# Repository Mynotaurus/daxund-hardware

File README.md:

# Daxund Hardware

kicad files for [daxund](https://zatzhing.me/blog/daxund)

terms of use is you can do what you want with it as long as you dont use AI. use your brains use your hands

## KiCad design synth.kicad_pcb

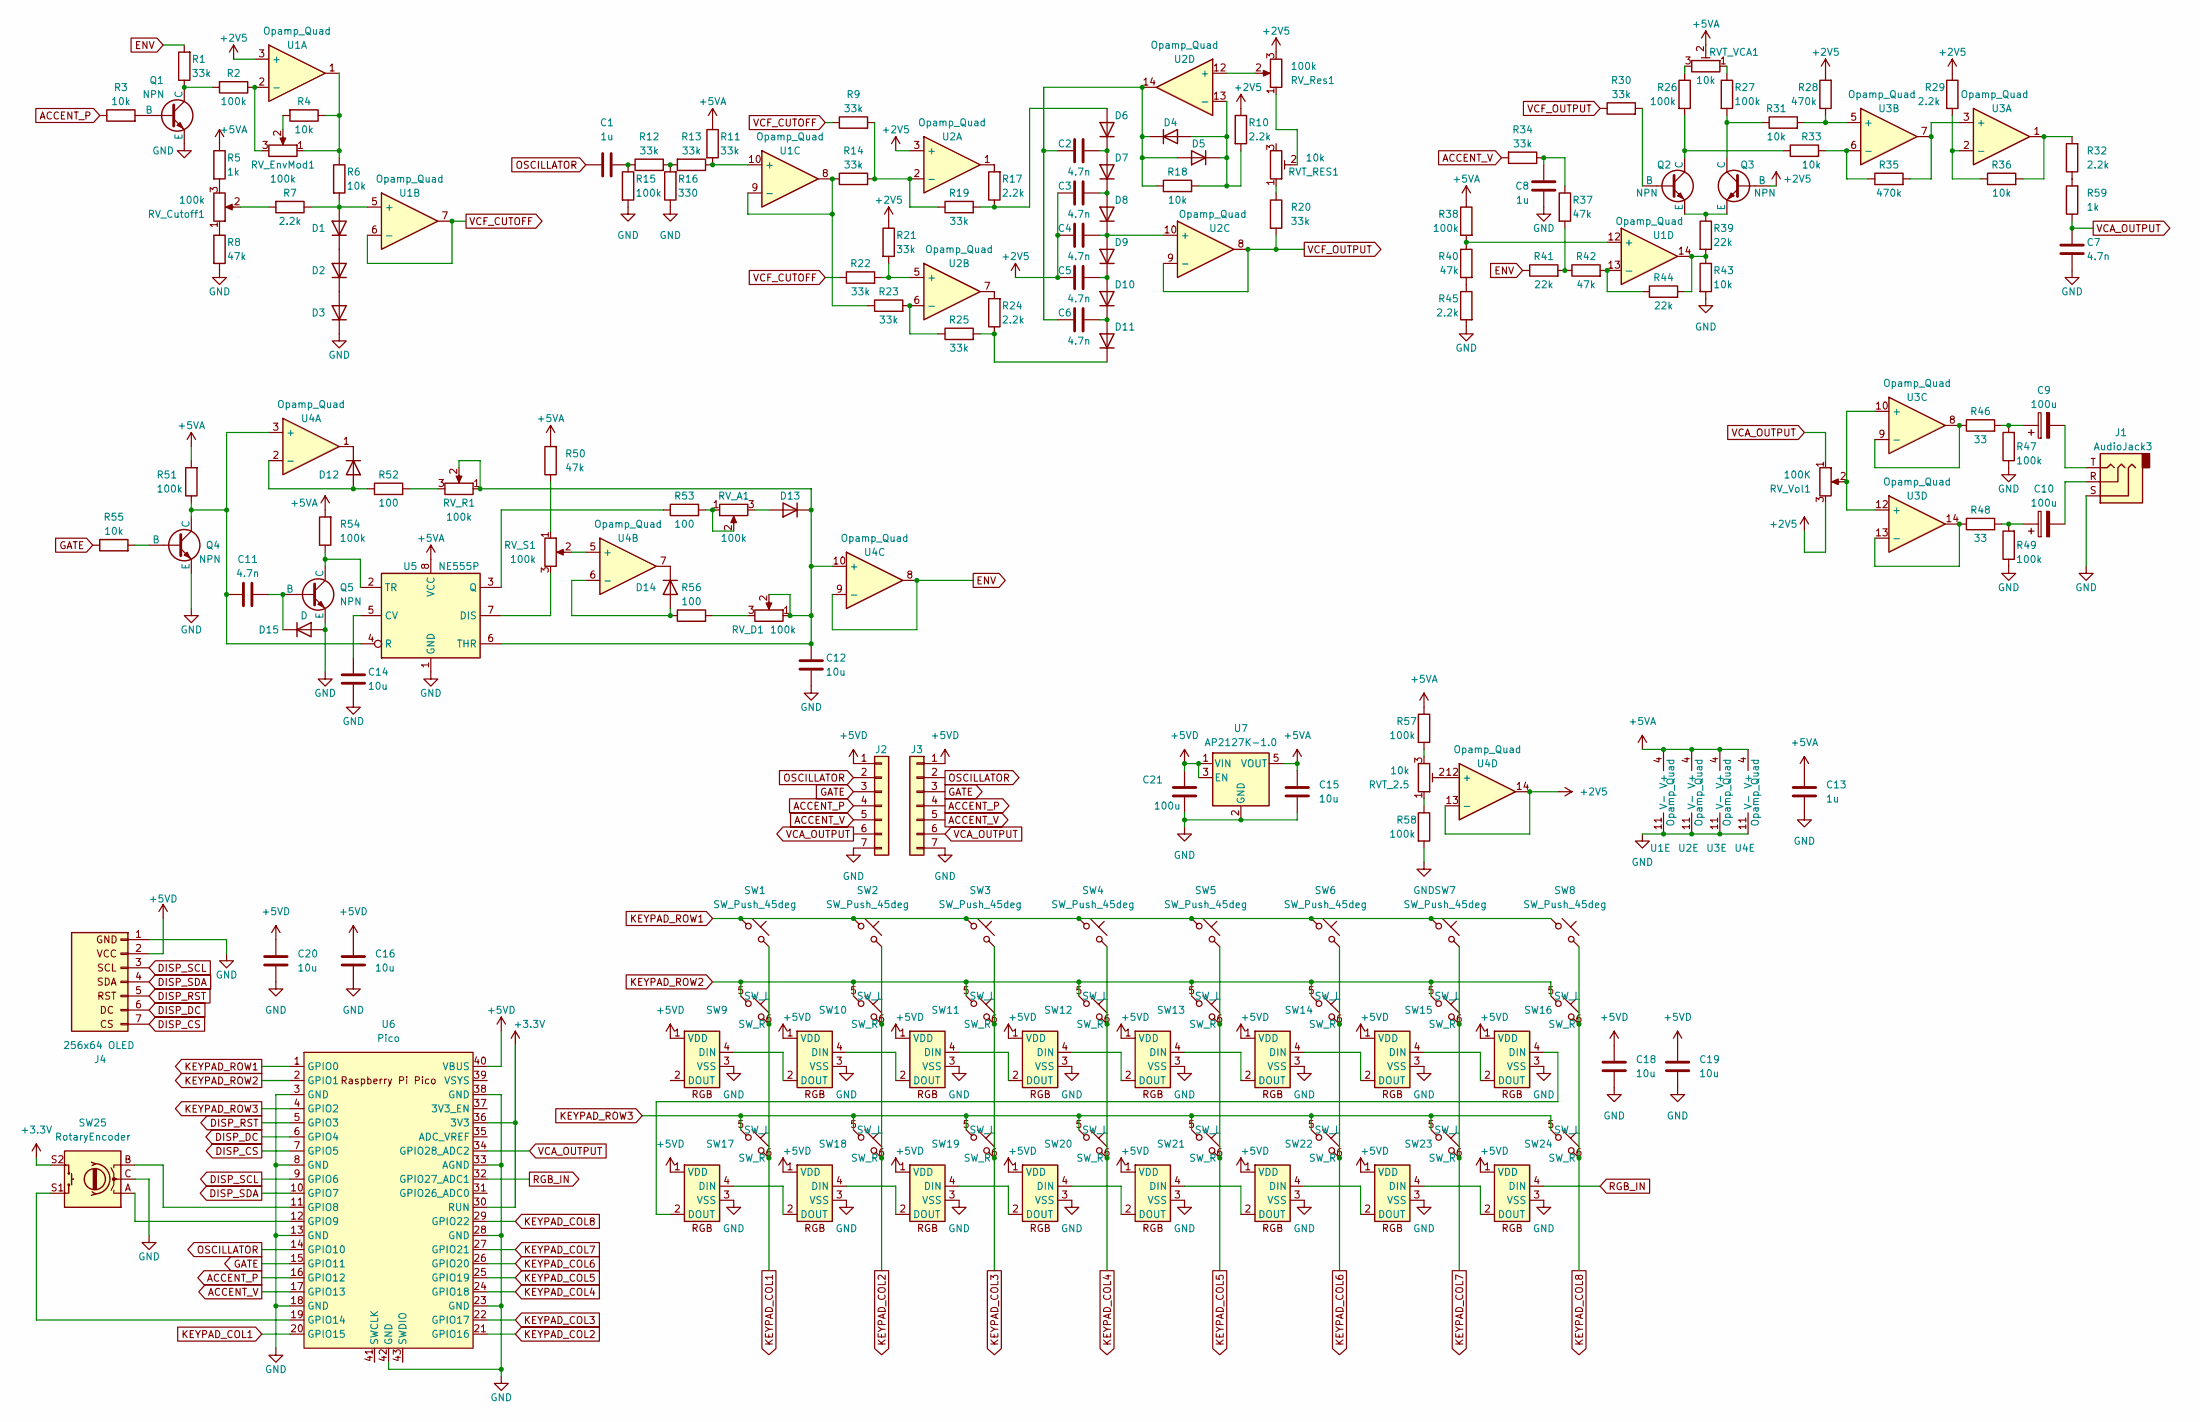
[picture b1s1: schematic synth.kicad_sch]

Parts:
C1, C8, C13: 1u; C_Rect_L7.0mm_W2.5mm_P5.00mm
C2, C3, C4, C5, C6, C7, C11: 4.7n; C_Rect_L7.0mm_W2.5mm_P5.00mm
C9, C10, C21: 100u; CP_Radial_D5.0mm_P2.50mm
C12, C14, C15, C16, C18, C19, C20: 10u; C_Rect_L7.0mm_W2.5mm_P5.00mm
D1, D2, D3, D4, D5, D6, D7, D8, D9, D10, D11, D12, D13, D14, D15: D; D_DO-35_SOD27_P7.62mm_Horizontal
J1: AudioJack3; Jack_3.5mm_CUI_SJ1-3525N_Horizontal
J2, J3: Conn_01x07; PinHeader_1x07_P2.54mm_Horizontal
J4: 256x64 OLED; oled
Q1, Q2, Q3, Q4, Q5: NPN; TO-92_Inline
R1, R9, R11, R12, R13, R14, R19, R20, R21, R22, R23, R25, R30, R34: 33k; R_Axial_DIN0207_L6.3mm_D2.5mm_P10.16mm_Horizontal
R2, R15, R26, R27, R38, R47, R49, R51, R54, R57, R58: 100k; R_Axial_DIN0207_L6.3mm_D2.5mm_P10.16mm_Horizontal
R3, R4, R6, R18, R31, R33, R36, R43, R55: 10k; R_Axial_DIN0207_L6.3mm_D2.5mm_P10.16mm_Horizontal
R5, R59: 1k; R_Axial_DIN0207_L6.3mm_D2.5mm_P10.16mm_Horizontal
R7, R10, R17, R24, R29, R32, R45: 2.2k; R_Axial_DIN0207_L6.3mm_D2.5mm_P10.16mm_Horizontal
R8, R37, R40, R42, R50: 47k; R_Axial_DIN0207_L6.3mm_D2.5mm_P10.16mm_Horizontal
R16: 330; R_Axial_DIN0207_L6.3mm_D2.5mm_P10.16mm_Horizontal
R28, R35: 470k; R_Axial_DIN0207_L6.3mm_D2.5mm_P10.16mm_Horizontal
R39, R41, R44: 22k; R_Axial_DIN0207_L6.3mm_D2.5mm_P10.16mm_Horizontal
R46, R48: 33; R_Axial_DIN0207_L6.3mm_D2.5mm_P10.16mm_Horizontal
R52, R53, R56: 100; R_Axial_DIN0207_L6.3mm_D2.5mm_P10.16mm_Horizontal
RVT_2.5: 10k; Potentiometer_ACP_CA9-V10_Vertical_Hole
RVT_RES1: 10k; Potentiometer_ACP_CA9-V10_Vertical_Hole
RVT_VCA1: 10k; Potentiometer_ACP_CA9-V10_Vertical_Hole
RV_A1: 100k; Potentiometer_Bourns_PTV09A-1_Single_Vertical
RV_Cutoff1: 100k; Potentiometer_Bourns_PTV09A-1_Single_Vertical
RV_D1: 100k; Potentiometer_Bourns_PTV09A-1_Single_Vertical
RV_EnvMod1: 100k; Potentiometer_Bourns_PTV09A-1_Single_Vertical
RV_R1: 100k; Potentiometer_Bourns_PTV09A-1_Single_Vertical
RV_Res1: 100k; Potentiometer_Bourns_PTV09A-1_Single_Vertical
RV_S1: 100k; Potentiometer_Bourns_PTV09A-1_Single_Vertical
RV_Vol1: 100K; Potentiometer_Bourns_PTV09A-1_Single_Vertical
SW1, SW2, SW3, SW4, SW5, SW6, SW7, SW8: SW_Push_45deg; SW_Cherry_MX_1.00u_PCB
SW9, SW10, SW11, SW12, SW13, SW14, SW15, SW16, SW17, SW18, SW19, SW20, SW21, SW22, SW23, SW24: button
SW25: RotaryEncoder; RotaryEncoder_Alps_EC11E-Switch_Vertical_H20mm
U1, U2, U3, U4: Opamp_Quad; DIP-14_W7.62mm
U5: NE555P; DIP-8_W7.62mm
U6: Pico; RPi_Pico_SMD_TH
U7: AP2127K-1.0; SOT-23-5

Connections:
+2V5: C3.1, C4.1, C5.1, Q3.2 (B), R10.1, R21.1, R28.2, R29.1, RV_Res1.3, RV_Vol1.3, U1.3 (+), U2.3 (+), U4.13 (-), U4.14
+3.3V: SW25.S2, U6.30 (RUN), U6.36 (3V3)
+5VA: C13.1, C15.1, R5.1, R11.1, R38.1, R50.2, R51.2, R54.2, R57.1, RVT_VCA1.2, U1.4 (V+), U2.4 (V+), U3.4 (V+), U4.4 (V+), U5.8 (VCC), U7.5 (VOUT)
+5VD: C16.1, C18.1, C19.1, C20.1, C21.1, J2.1, J3.1, J4.2 (VCC), SW9.1 (VDD), SW10.1 (VDD), SW11.1 (VDD), SW12.1 (VDD), SW13.1 (VDD), SW14.1 (VDD), SW15.1 (VDD), SW16.1 (VDD), SW17.1 (VDD), SW18.1 (VDD), SW19.1 (VDD), SW20.1 (VDD), SW21.1 (VDD), SW22.1 (VDD), SW23.1 (VDD), SW24.1 (VDD), U6.40 (VBUS), U7.1 (VIN), U7.3 (EN)
ACCENT_P: J2.4, J3.4, R3.1, U6.16 (GPIO12)
ACCENT_V: J2.5, J3.5, R34.2, U6.17 (GPIO13)
DISP_CS: J4.7 (CS), U6.7 (GPIO5)
DISP_DC: J4.6 (DC), U6.6 (GPIO4)
DISP_RST: J4.5 (RST), U6.5 (GPIO3)
DISP_SCL: J4.3 (SCL), U6.9 (GPIO6)
DISP_SDA: J4.4 (SDA), U6.10 (GPIO7)
ENV: R1.2, R41.1, U4.8, U4.9 (-)
GATE: J2.3, J3.3, R55.1, U6.15 (GPIO11)
GND: C7.2, C8.2, C12.2, C13.2, C14.1, C15.2, C16.2, C18.2, C19.2, C20.2, C21.2, D3.1 (K), D15.2 (A), J1.S, J2.7, J3.7, J4.1 (GND), Q1.3 (E), Q4.3 (E), Q5.3 (E), R8.2, R15.2, R16.1, R43.2, R45.2, R47.1, R49.1, R58.2, SW9.3 (VSS), SW10.3 (VSS), SW11.3 (VSS), SW12.3 (VSS), SW13.3 (VSS), SW14.3 (VSS), SW15.3 (VSS), SW16.3 (VSS), SW17.3 (VSS), SW18.3 (VSS), SW19.3 (VSS), SW20.3 (VSS), SW21.3 (VSS), SW22.3 (VSS), SW23.3 (VSS), SW24.3 (VSS), SW25.C, U1.11 (V-), U2.11 (V-), U3.11 (V-), U4.11 (V-), U5.1 (GND), U6.3 (GND), U6.8 (GND), U6.13 (GND), U6.18 (GND), U6.23 (GND), U6.28 (GND), U6.33 (AGND), U6.38 (GND), U6.42 (GND), U7.2 (GND)
KEYPAD_COL1: SW1.2, SW9.6 (SW_R), SW17.6 (SW_R), U6.20 (GPIO15)
KEYPAD_COL2: SW2.2, SW10.6 (SW_R), SW18.6 (SW_R), U6.21 (GPIO16)
KEYPAD_COL3: SW3.2, SW11.6 (SW_R), SW19.6 (SW_R), U6.22 (GPIO17)
KEYPAD_COL4: SW4.2, SW12.6 (SW_R), SW20.6 (SW_R), U6.24 (GPIO18)
KEYPAD_COL5: SW5.2, SW13.6 (SW_R), SW21.6 (SW_R), U6.25 (GPIO19)
KEYPAD_COL6: SW6.2, SW14.6 (SW_R), SW22.6 (SW_R), U6.26 (GPIO20)
KEYPAD_COL7: SW7.2, SW15.6 (SW_R), SW23.6 (SW_R), U6.27 (GPIO21)
KEYPAD_COL8: SW8.2, SW16.6 (SW_R), SW24.6 (SW_R), U6.29 (GPIO22)
KEYPAD_ROW1: SW1.1, SW2.1, SW3.1, SW4.1, SW5.1, SW6.1, SW7.1, SW8.1, U6.1 (GPIO0)
KEYPAD_ROW2: SW9.5 (SW_L), SW10.5 (SW_L), SW11.5 (SW_L), SW12.5 (SW_L), SW13.5 (SW_L), SW14.5 (SW_L), SW15.5 (SW_L), SW16.5 (SW_L), U6.2 (GPIO1)
KEYPAD_ROW3: SW17.5 (SW_L), SW18.5 (SW_L), SW19.5 (SW_L), SW20.5 (SW_L), SW21.5 (SW_L), SW22.5 (SW_L), SW23.5 (SW_L), SW24.5 (SW_L), U6.4 (GPIO2)
unnamed: C1.1, R12.1, R15.1
unnamed: C8.1, R34.1, R37.1
unnamed: C9.1, R46.2, R47.2
unnamed: C9.2, J1.T
unnamed: C10.1, R48.2, R49.2
unnamed: C10.2, J1.R
unnamed: D1.2 (A), R6.2, R7.1, U1.5 (+)
unnamed: D1.1 (K), D2.2 (A)
unnamed: D2.1 (K), D3.2 (A)
unnamed: D4.2 (A), D5.1 (K), R10.2, R18.2, U2.13 (-)
unnamed: C2.1, C6.1, D4.1 (K), D5.2 (A), R18.1, U2.14
unnamed: D6.2 (A), R17.1, R19.2
unnamed: C2.2, D6.1 (K), D7.2 (A)
unnamed: C3.2, D7.1 (K), D8.2 (A)
unnamed: C4.2, D8.1 (K), D9.2 (A), U2.10 (+)
unnamed: C5.2, D9.1 (K), D10.2 (A)
unnamed: C6.2, D10.1 (K), D11.2 (A)
unnamed: D11.1 (K), R24.1, R25.2
unnamed: D12.2 (A), R52.1, U4.2 (-)
unnamed: D12.1 (K), U4.1
unnamed: D13.2 (A), RV_A1.3
unnamed: C12.1, D13.1 (K), RV_D1.1, RV_D1.2, RV_R1.1, RV_R1.2, U4.10 (+), U5.6 (THR)
unnamed: D14.2 (A), R56.1, U4.6 (-)
unnamed: D14.1 (K), U4.7
unnamed: C11.2, D15.1 (K), Q5.2 (B)
unnamed: Q1.2 (B), R3.2
unnamed: Q1.1 (C), R1.1, R2.2
unnamed: Q2.2 (B), R30.2
unnamed: Q2.1 (C), R26.2, R33.1
unnamed: Q2.3 (E), Q3.3 (E), R39.1
unnamed: Q3.1 (C), R27.2, R31.1
unnamed: Q4.2 (B), R55.2
unnamed: C11.1, Q4.1 (C), R51.1, U4.3 (+), U5.4 (R)
unnamed: Q5.1 (C), R54.1, U5.2 (TR)
unnamed: R4.1, R6.1, RV_EnvMod1.1, U1.1
unnamed: R4.2, RV_EnvMod1.2
unnamed: R5.2, RV_Cutoff1.3
unnamed: R7.2, RV_Cutoff1.2
unnamed: R8.1, RV_Cutoff1.1
unnamed: R12.2, R13.2, R16.2
unnamed: R17.2, U2.1
unnamed: R20.1, RVT_RES1.1
unnamed: R24.2, U2.7
unnamed: R26.1, RVT_VCA1.3
unnamed: R27.1, RVT_VCA1.1
unnamed: R32.1, R59.2
unnamed: R32.2, R36.2, U3.1
unnamed: R37.2, R41.2, R42.1
unnamed: R39.2, R43.1, R44.2, U1.14
unnamed: R40.2, R45.1
unnamed: R50.1, RV_S1.1
unnamed: R52.2, RV_R1.3
unnamed: R53.2, RV_A1.1, RV_A1.2
unnamed: R56.2, RV_D1.3
unnamed: R57.2, RVT_2.5.3
unnamed: R58.1, RVT_2.5.1
unnamed: RVT_RES1.2, RV_Res1.1
unnamed: SW10.4 (DIN), SW11.2 (DOUT)
unnamed: SW9.4 (DIN), SW10.2 (DOUT)
unnamed: SW11.4 (DIN), SW12.2 (DOUT)
unnamed: SW12.4 (DIN), SW13.2 (DOUT)
unnamed: SW13.4 (DIN), SW14.2 (DOUT)
unnamed: SW14.4 (DIN), SW15.2 (DOUT)
unnamed: SW15.4 (DIN), SW16.2 (DOUT)
unnamed: SW16.4 (DIN), SW17.2 (DOUT)
unnamed: SW17.4 (DIN), SW18.2 (DOUT)
unnamed: SW18.4 (DIN), SW19.2 (DOUT)
unnamed: SW19.4 (DIN), SW20.2 (DOUT)
unnamed: SW20.4 (DIN), SW21.2 (DOUT)
unnamed: SW21.4 (DIN), SW22.2 (DOUT)
unnamed: SW22.4 (DIN), SW23.2 (DOUT)
unnamed: SW23.4 (DIN), SW24.2 (DOUT)
unnamed: R2.1, RV_EnvMod1.3, U1.2 (-)
unnamed: R11.2, R13.1, U1.10 (+)
unnamed: R14.1, R23.1, U1.8, U1.9 (-)
unnamed: R38.2, R40.1, U1.12 (+)
unnamed: R42.2, R44.1, U1.13 (-)
unnamed: R9.2, R14.2, R19.1, U2.2 (-)
unnamed: R21.2, R22.2, U2.5 (+)
unnamed: R23.2, R25.1, U2.6 (-)
unnamed: RV_Res1.2, U2.12 (+)
unnamed: R35.2, U3.3 (+), U3.7
unnamed: R29.2, R36.1, U3.2 (-)
unnamed: R28.1, R31.2, U3.5 (+)
unnamed: R33.2, R35.1, U3.6 (-)
unnamed: RV_Vol1.2, U3.10 (+), U3.12 (+)
unnamed: R46.1, U3.8, U3.9 (-)
unnamed: R48.1, U3.13 (-), U3.14
unnamed: RV_S1.2, U4.5 (+)
unnamed: RVT_2.5.2, U4.12 (+)
unnamed: C14.2, U5.5 (CV)
unnamed: RV_S1.3, U5.7 (DIS)
unnamed: R53.1, U5.3 (Q)
unnamed: SW25.B, U6.11 (GPIO8)
unnamed: SW25.A, U6.12 (GPIO9)
unnamed: SW25.S1, U6.19 (GPIO14)
OSCILLATOR: C1.2, J2.2, J3.2, U6.14 (GPIO10)
RGB_IN: SW24.4 (DIN), U6.32 (GPIO27_ADC1)
VCA_OUTPUT: C7.1, J2.6, J3.6, R59.1, RV_Vol1.1, U6.34 (GPIO28_ADC2)
VCF_CUTOFF: R9.1, R22.1, U1.6 (-), U1.7
VCF_OUTPUT: R20.2, R30.1, U2.8, U2.9 (-)

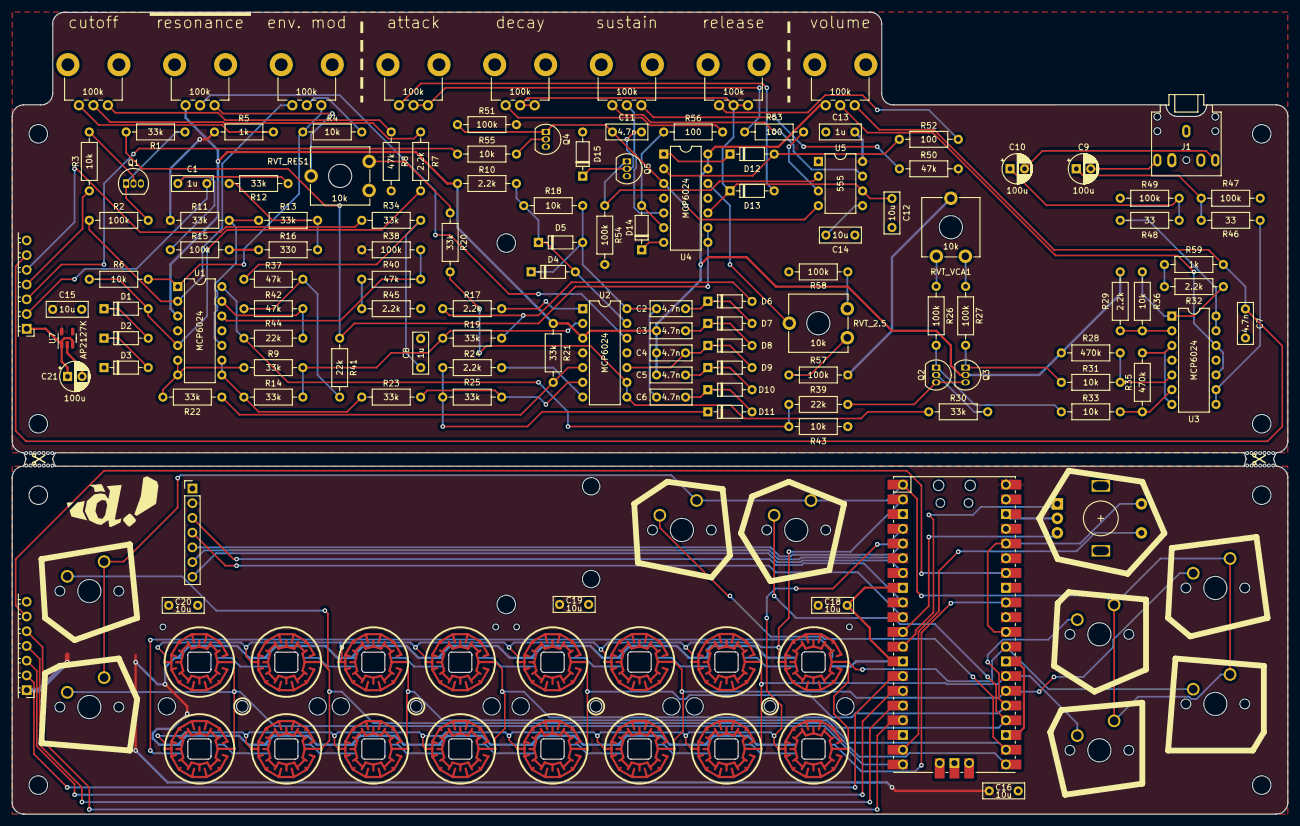
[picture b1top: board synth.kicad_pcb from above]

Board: 2 copper layers, 220.0 x 138.3 mm, 146 parts (0 on the bottom side), 126 nets.
